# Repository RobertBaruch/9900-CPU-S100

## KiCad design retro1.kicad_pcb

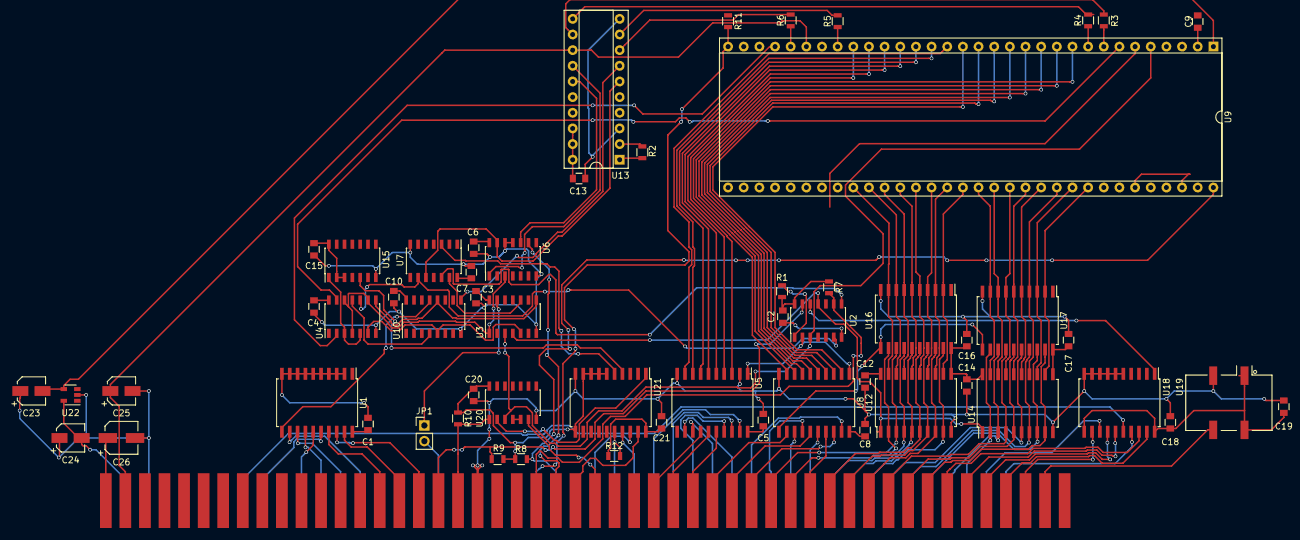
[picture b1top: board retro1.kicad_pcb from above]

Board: 2 copper layers, 59 parts (0 on the bottom side), 144 nets.

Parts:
C1, C2, C3, C4, C5, C6, C7, C8, C9, C10, C12, C13, C14, C15, C16, C17, C18, C19, C20, C21: 100n; C_0805
C23, C25: 10u; CP_Elec_4x4.5
C24: 1u; CP_Elec_4x4.5
C26: 100u; CP_Elec_5x5.3
JP1: MWRT JUMPER; Pin_Header_Straight_1x02_Pitch2.54mm
P1: S100_CARD_EDGE; S-100_card_edge
R1, R7, R8, R9, R10, R11, R12: 1k; R_0805
R2: 130R; R_0805
R3, R4, R5, R6: 16R; R_0805
U1, U5, U8, U12, U14, U16, U17, U18, U21: 74F573; SOIC-20W_7.5x12.8mm_Pitch1.27mm
U2, U20: 74F04; SOIC-14_3.9x8.7mm_Pitch1.27mm
U3: 74F02; SOIC-14_3.9x8.7mm_Pitch1.27mm
U4: 74F08; SOIC-14_3.9x8.7mm_Pitch1.27mm
U6, U15: 74F74; SOIC-14_3.9x8.7mm_Pitch1.27mm
U7: 74LS32; SOIC-14_3.9x8.7mm_Pitch1.27mm
U9: TMS9900; DIP-64_W22.86mm_Socket
U10: 74F175; SOIC-16_3.9x9.9mm_Pitch1.27mm
U13: TIM9904; DIP-20_W7.62mm_Socket
U19: SG-615P 2.0000MC0; Oscillator_SMD_Epson_SG615-4pin_8.8x5.08mm
U22: MIC5270-5.0BM5; SOT-23-5

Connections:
+5V: C1.1, C2.1, C3.1, C4.1, C5.1, C6.1, C7.1, C8.1, C9.1, C10.1, C12.1, C13.1, C14.1, C15.1, C16.1, C17.1, C18.1, C19.1, C20.1, C21.1, C26.1, P1.1, P1.51, R1.1, R7.1, R8.1, R9.1, R10.1, R11.1, R12.1, U1.20, U2.14, U3.14, U4.14, U5.20, U6.2, U6.4, U6.14, U7.14, U8.20, U9.2, U9.59, U9.62, U10.16, U12.11, U12.20, U13.18, U13.19, U13.20, U14.11, U14.20, U15.2, U15.3, U15.14, U16.20, U17.20, U18.11, U18.20, U19.1, U19.4, U20.14, U21.6, U21.7, U21.8, U21.9, U21.11, U21.20
+12V: C25.1, P1.2, U9.27, U13.13
-5V: C23.2, U9.1, U22.4
-12VA: C24.2, P1.52, U22.5
//ADSB: P1.22, R1.2, U2.1
//CDSB: P1.19, R10.2, U20.1
//CPU_pSTVAL: U10.14, U21.2
//DATA_OUT: U7.11, U16.1, U17.1, U18.4
//DBIN: U2.6, U4.10, U7.9
//DODSB: P1.23, R7.2, U2.9
//HOLD: P1.74, R8.2, U9.64
//INT: P1.73, R11.2, U9.32
//MEMEN: U3.2, U9.63
//RESET: P1.75, U9.6, U10.1
//SDSB: P1.18, R9.2, U2.13
//WE: U7.2, U9.61
//WE': U7.3, U21.5
//pSTVAL: P1.25, U21.19
//pWR: P1.77, R12.2, U3.12, U21.16
//sMEMR: U2.11, U3.4, U12.1, U14.1
//sMEMW: U3.10, U7.13
//sWO: P1.97, U18.17
//sXTRQ: P1.58, U18.16
//Φ1: U6.1, U13.14
//Φ2: U6.10, U13.15
//Φ3: U10.9, U13.7
//Φ4: U6.13, U7.10, U13.6
/A1: U5.3, U9.24
/A2: U5.4, U9.23
/A3: U5.5, U9.22
/A4: U5.6, U9.21
/A5: U5.7, U9.20
/A6: U5.8, U9.19
/A7: U5.9, U9.18
/A8: U8.2, U9.17
/A9: U8.3, U9.16
/A10: U8.4, U9.15
/A11: U8.5, U9.14
/A12: U8.6, U9.13
/A13: U8.7, U9.12
/A14: U8.8, U9.11
/A15: U8.9, U9.10
/ADSB: U1.1, U2.2, U5.1, U8.1
/BA0: P1.79, U5.19
/BA1: P1.80, U5.18
/BA2: P1.81, U5.17
/BA3: P1.31, U5.16
/BA4: P1.30, U5.15
/BA5: P1.29, U5.14
/BA6: P1.82, U5.13
/BA7: P1.83, U5.12
/BA8: P1.84, U8.19
/BA9: P1.34, U8.18
/BA10: P1.37, U8.17
/BA11: P1.87, U8.16
/BA12: P1.33, U8.15
/BA13: P1.85, U8.14
/BA14: P1.86, U8.13
/BA15: P1.32, U8.12
/BA16: P1.16, U1.19
/BA17: P1.17, U1.18
/BA18: P1.15, U1.17
/BA19: P1.59, U1.16
/BA20: P1.61, U1.15
/BA21: P1.62, U1.14
/BA22: P1.63, U1.13
/BA23: P1.64, U1.12
/BD0: P1.36, U12.2, U16.12
/BD1: P1.35, U12.3, U16.13
/BD2: P1.88, U12.4, U16.14
/BD3: P1.89, U12.5, U16.15
/BD4: P1.38, U12.6, U16.16
/BD5: P1.39, U12.7, U16.17
/BD6: P1.40, U12.8, U16.18
/BD7: P1.90, U12.9, U16.19
/BD8: P1.95, U14.2, U17.12
/BD9: P1.94, U14.3, U17.13
/BD10: P1.41, U14.4, U17.14
/BD11: P1.42, U14.5, U17.15
/BD12: P1.91, U14.6, U17.16
/BD13: P1.92, U14.7, U17.17
/BD14: P1.93, U14.8, U17.18
/BD15: P1.43, U14.9, U17.19
/CDSB: U20.2, U21.1
/CLOCK: P1.49, U19.3
/CPU_pDBIN: U15.5, U21.4
/CPU_pSYNC: U1.11, U5.11, U6.5, U8.11, U10.13, U16.11, U17.11, U21.3
/CPU_sM1: U7.6, U18.3
/D0: U9.41, U12.19, U16.9
/D1: U9.42, U12.18, U16.8
/D2: U9.43, U12.17, U16.7
/D3: U9.44, U12.16, U16.6
/D4: U9.45, U12.15, U16.5
/D5: U9.46, U12.14, U16.4
/D6: U9.47, U12.13, U16.3
/D7: U9.48, U12.12, U16.2
/D8: U9.49, U14.19, U17.9
/D9: U9.50, U14.18, U17.8
/D10: U9.51, U14.17, U17.7
/D11: U9.52, U14.16, U17.6
/D12: U9.53, U14.15, U17.5
/D13: U9.54, U14.14, U17.4
/D14: U9.55, U14.13, U17.3
/D15: U9.56, U14.12, U17.2
/DBIN: U4.2, U9.29
/DBIN': U2.5, U4.3, U4.5, U15.1
/DODSB: U2.8, U7.12
/HOLDA: U2.3, U3.3, U7.1, U9.5, U20.3
/IAQ: U4.13, U9.7
/M1: U4.11, U7.4, U10.4
/MEMEN: U3.1, U4.4, U4.9, U4.12, U6.3
/MEMR: U3.5, U4.6, U10.5
/MEMW: U3.8, U4.8, U10.12
/MWRT: JP1.2, P1.68
/SDSB: U2.12, U18.1
/pDBIN: P1.78, U21.17
/pHLDA: P1.26, U20.6
/pSYNC: P1.76, U21.18
/sHLTA: P1.48, U18.12
/sINP: P1.46, U18.14
/sINTA: P1.96, U18.13
/sM1: P1.44, U18.18
/sMEMR: P1.47, U18.19
/sOUT: P1.45, U3.11, U18.15
/Φ: P1.24, U6.9
/Φ1_12V: R3.1, U9.8
/Φ2_12V: R4.1, U9.9
/Φ3_12V: R6.1, U9.28
/Φ4_12V: R5.1, U9.25
GND: C1.2, C2.2, C3.2, C4.2, C5.2, C6.2, C7.2, C8.2, C9.2, C10.2, C12.2, C13.2, C14.2, C15.2, C16.2, C17.2, C18.2, C19.2, C20.2, C21.2, C23.1, C24.1, C25.2, C26.2, P1.20, P1.50, P1.53, P1.70, P1.100, U1.2, U1.3, U1.4, U1.5, U1.6, U1.7, U1.8, U1.9, U1.10, U2.7, U3.7, U4.7, U5.2, U5.10, U6.7, U6.11, U6.12, U7.7, U8.10, U9.26, U9.40, U10.8, U12.10, U13.3, U13.10, U14.10, U15.7, U16.10, U17.10, U18.5, U18.6, U18.7, U18.8, U18.9, U18.10, U19.2, U20.7, U21.10, U22.2
unnamed: JP1.1, U3.13
unnamed: R2.1, U13.1
unnamed: R2.2, U13.2
unnamed: R3.2, U13.12
unnamed: R4.2, U13.11
unnamed: R5.2, U13.9
unnamed: R6.2, U13.8
unnamed: U2.4, U4.1
unnamed: U7.5, U10.2
unnamed: U3.6, U10.7
unnamed: U3.9, U10.10
unnamed: U7.8, U15.4
unnamed: U2.10, U18.2
unnamed: U20.4, U20.5

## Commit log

2017-08-26 Initial commit, partway through PCB.
